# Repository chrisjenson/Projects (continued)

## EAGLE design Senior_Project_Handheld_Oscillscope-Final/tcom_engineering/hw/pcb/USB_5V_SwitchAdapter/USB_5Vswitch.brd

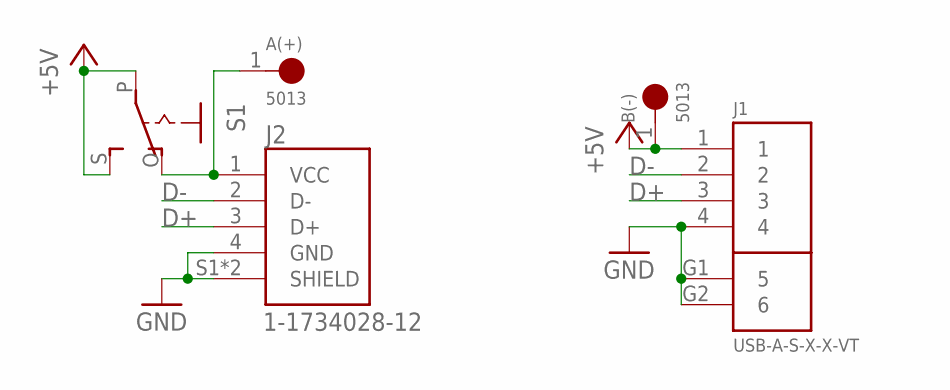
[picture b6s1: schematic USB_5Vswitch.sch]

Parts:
A(+): 5013; TESTPOINT_5013
B(-): 5013; TESTPOINT_5013
J1: USB-A-S-X-X-VT
J2: 1-1734028-12; TE_1-1734028-2
S1: EG1218S; EG1218

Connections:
+5V: B(-).1, J1.1, S1.P, S1.S
D+: J1.3, J2.3 (D+)
D-: J1.2, J2.2 (D-)
GND: J1.4, J1.G1 (5), J1.G2 (6), J2.4 (GND), J2.S1 (SHIELD), J2.S2 (SHIELD)
unnamed: A(+).1, J2.1 (VCC), S1.O

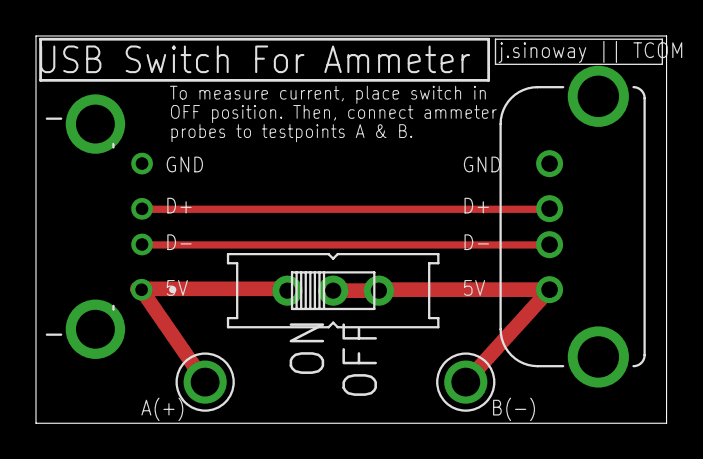
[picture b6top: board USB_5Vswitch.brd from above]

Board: 2 copper layers, 35.0 x 21.5 mm, 5 parts (0 on the bottom side), 5 nets.

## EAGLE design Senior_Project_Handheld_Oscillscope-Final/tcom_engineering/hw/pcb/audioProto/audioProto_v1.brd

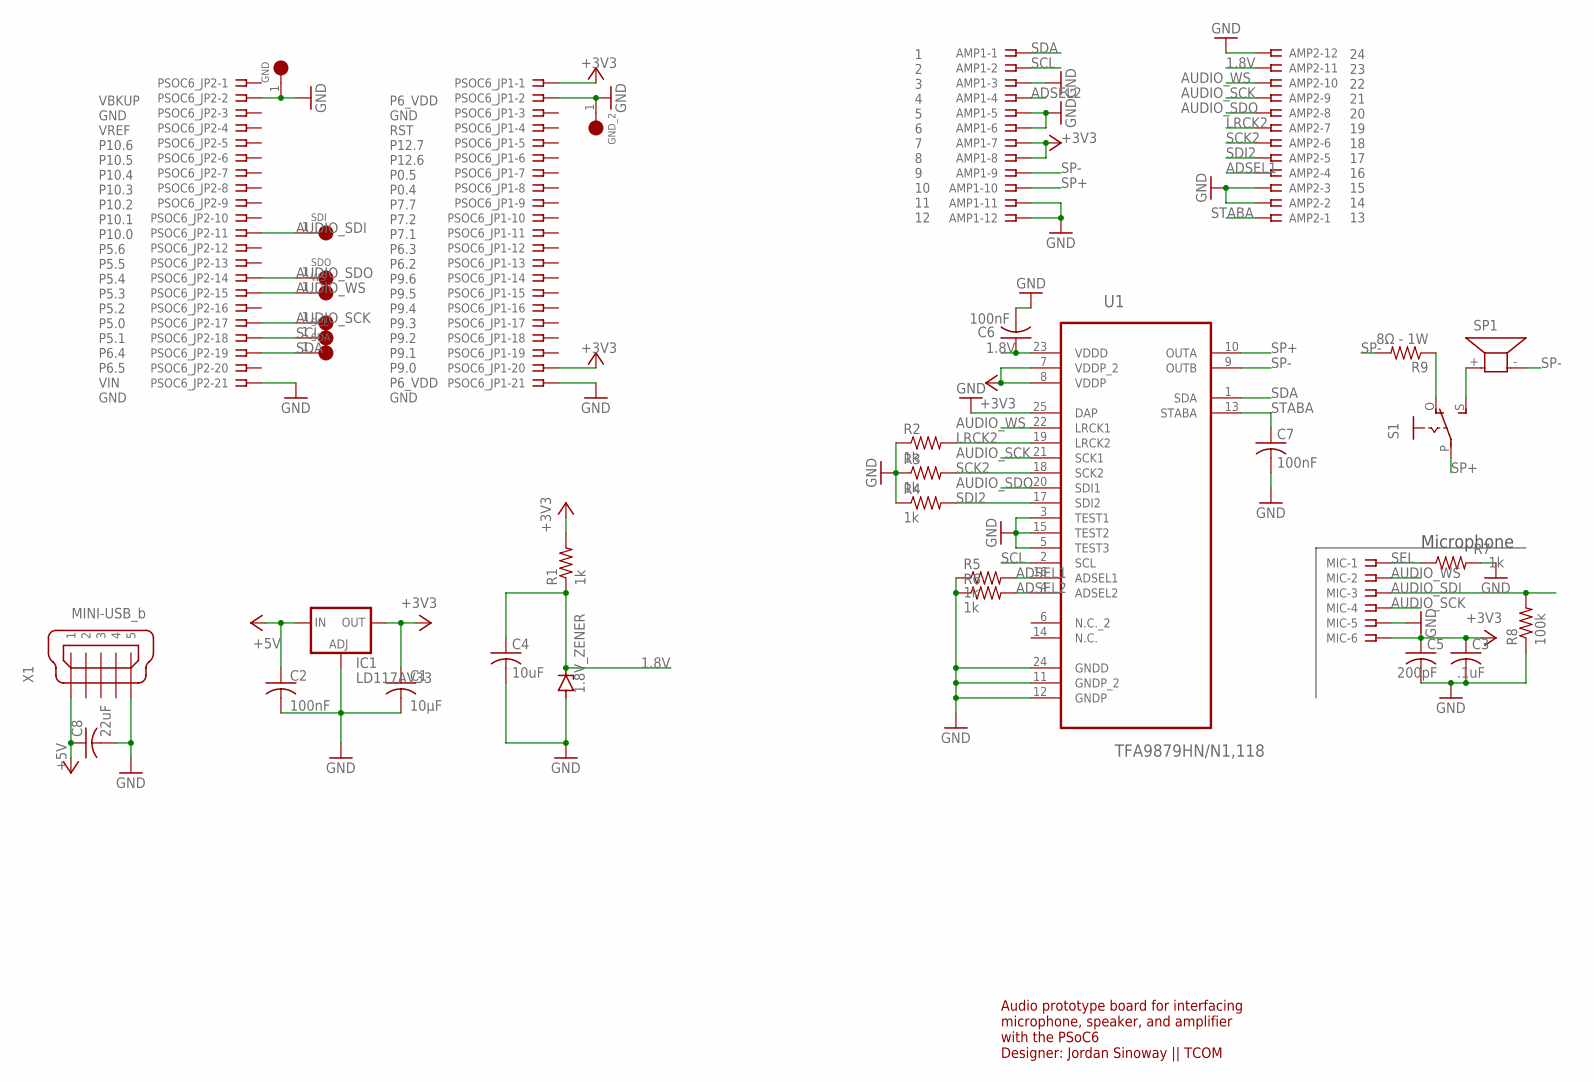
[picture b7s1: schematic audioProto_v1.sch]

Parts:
1.8V_ZENER: BZV10; DO34Z7
AMP1, AMP2: SSW-112-02-G-S
C1: 10μF; C050-024X044
C2, C6, C7: 100nF; C050-024X044
C3: .1uF; C050-024X044
C4: 10uF; C050-024X044
C5: 200pF; C050-024X044
C8: 22uF; C050-024X044
GND: 5013; TESTPOINT_5013
GND_2: 5013; TESTPOINT_5013
IC1: LD117AV33; TO220L1
MIC: SSW-106-02-G-S
PSOC6_JP1, PSOC6_JP2: SSW-121-02-G-S
R1, R2, R3, R4, R5, R6: 1k; 0204/7
R7: 1k; 0207/9
R8: 100k; 0207/9
R9: 8Ω - 1W; 0207/10
S1: EG1218S; EG1218
SCK: 5013; TESTPOINT_5013
SCL: 5013; TESTPOINT_5013
SDA: 5013; TESTPOINT_5013
SDI: 5013; TESTPOINT_5013
SDO: 5013; TESTPOINT_5013
SP1: KSS1201
U1: TFA9879HN/N1,118; QFN50P260X260X100-25N
WS: 5013; TESTPOINT_5013
X1: MINI-USB_b; 32005-601

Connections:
1.8V: 1.8V_ZENER.C, AMP2.11, C4.1, C6.1, R1.1, U1.23 (VDDD)
+3V3: AMP1.7, AMP1.8, C1.1, C3.1, C5.1, IC1.2 (OUT), MIC.6, PSOC6_JP1.1, PSOC6_JP1.20, R1.2, U1.7 (VDDP_2), U1.8 (VDDP)
+5V: C2.1, C8.1, IC1.3 (IN), X1.1
ADSEL1: AMP2.4, R5.2, U1.16 (ADSEL1)
ADSEL2: AMP1.4, R6.2, U1.4 (ADSEL2)
AUDIO_SCK: AMP2.9, MIC.4, PSOC6_JP2.17, SCK.1, U1.21 (SCK1)
AUDIO_SDI: MIC.3, PSOC6_JP2.11, R8.2, SDI.1
AUDIO_SDO: AMP2.8, PSOC6_JP2.14, SDO.1, U1.20 (SDI1)
AUDIO_WS: AMP2.10, MIC.2, PSOC6_JP2.15, U1.22 (LRCK1), WS.1
GND: 1.8V_ZENER.A, AMP1.3, AMP1.5, AMP1.6, AMP1.11, AMP1.12, AMP2.2, AMP2.3, AMP2.12, C1.2, C2.2, C3.2, C4.2, C5.2, C6.2, C7.2, C8.2, GND.1, GND_2.1, IC1.1 (ADJ), MIC.5, PSOC6_JP1.2, PSOC6_JP1.21, PSOC6_JP2.2, PSOC6_JP2.21, R2.1, R3.1, R4.1, R5.1, R6.1, R7.2, R8.1, U1.3 (TEST1), U1.5 (TEST3), U1.11 (GNDP_2), U1.12 (GNDP), U1.15 (TEST2), U1.24 (GNDD), U1.25 (DAP), X1.5
LRCK2: AMP2.7, R2.2, U1.19 (LRCK2)
unnamed: R9.1, S1.O
unnamed: S1.S, SP1.+ (1)
SCK2: AMP2.6, R3.2, U1.18 (SCK2)
SCL: AMP1.2, PSOC6_JP2.18, SCL.1, U1.2 (SCL)
SDA: AMP1.1, PSOC6_JP2.19, SDA.1, U1.1 (SDA)
SDI2: AMP2.5, R4.2, U1.17 (SDI2)
SEL: MIC.1, R7.1
SP+: AMP1.10, S1.P, U1.10 (OUTA)
SP-: AMP1.9, R9.2, SP1.- (2), U1.9 (OUTB)
STABA: AMP2.1, C7.1, U1.13 (STABA)

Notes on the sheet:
VBKUP GND VREF P10.6 P10.5 P10.4 P10.3 P10.2 P10.1 P10.0 P5.6 P5.5 P5.4 P5.3 P5.2 P5.0 P5.1 P6.4 P6.5 VIN GND
P6_VDD GND RST P12.7 P12.6 P0.5 P0.4 P7.7 P7.2 P7.1 P6.3 P6.2 P9.6 P9.5 P9.4 P9.3 P9.2 P9.1 P9.0 P6_VDD GND
Microphone
1 2 3 4 5 6 7 8 9 10 11 12
24 23 22 21 20 19 18 17 16 15 14 13
Audio prototype board for interfacing microphone, speaker, and amplifier with the PSoC6 Designer: Jordan Sinoway || TCOM

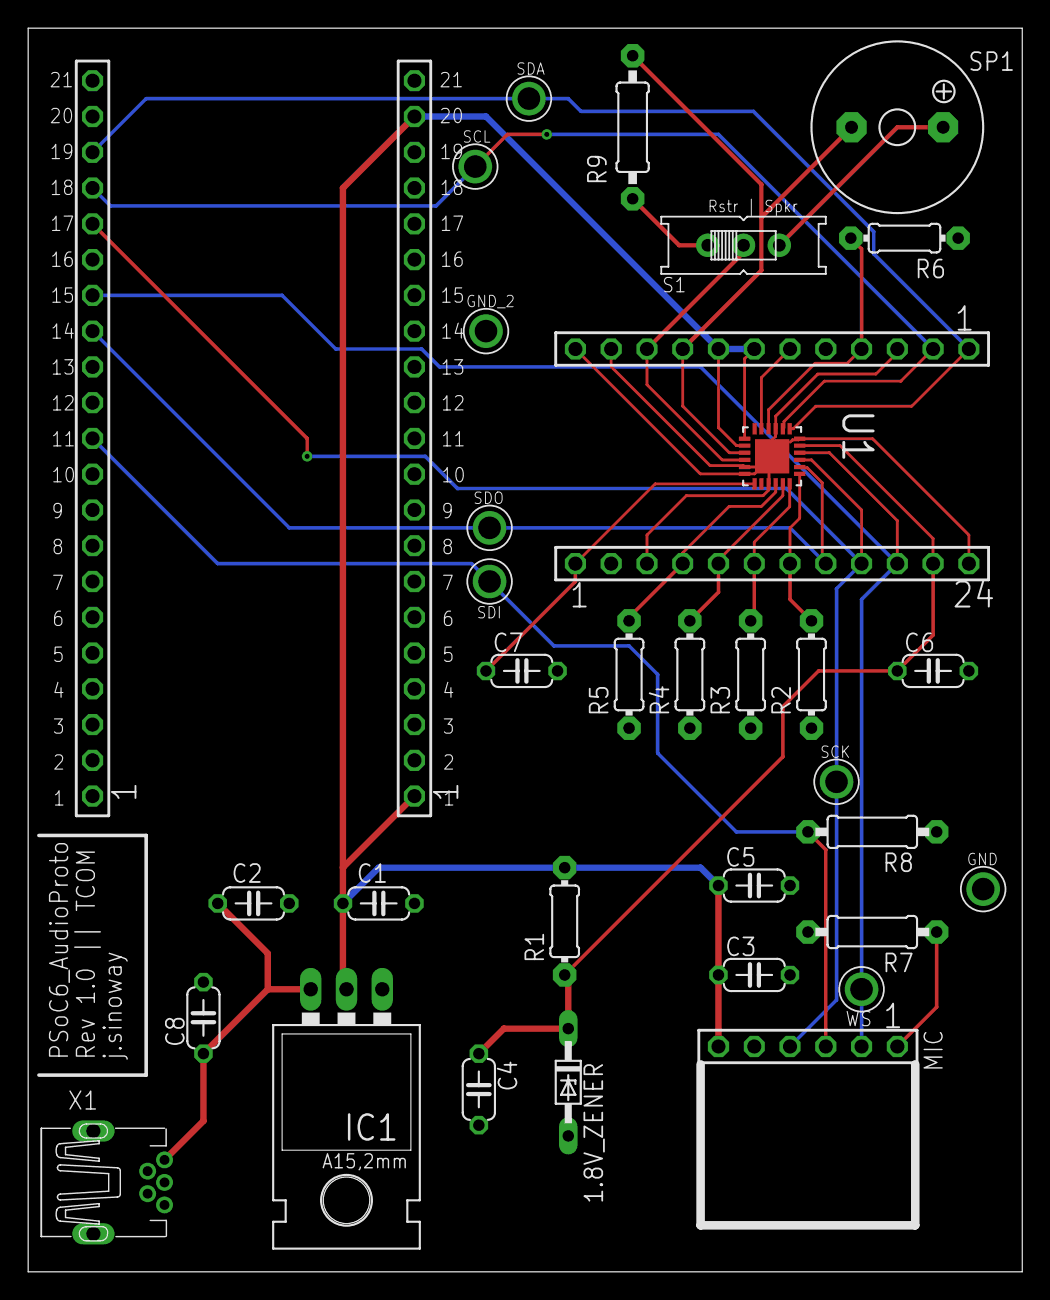
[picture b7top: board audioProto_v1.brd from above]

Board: 2 copper layers, 70.6 x 88.3 mm, 36 parts (0 on the bottom side), 21 nets.

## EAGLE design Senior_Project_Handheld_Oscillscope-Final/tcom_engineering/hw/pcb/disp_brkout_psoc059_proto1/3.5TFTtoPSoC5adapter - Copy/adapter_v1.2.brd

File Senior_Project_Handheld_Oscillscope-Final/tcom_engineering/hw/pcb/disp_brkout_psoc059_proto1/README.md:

# disp_brkout_psoc059_proto1
Eagle database for display breakout board to PSoC 5LP 059 board.

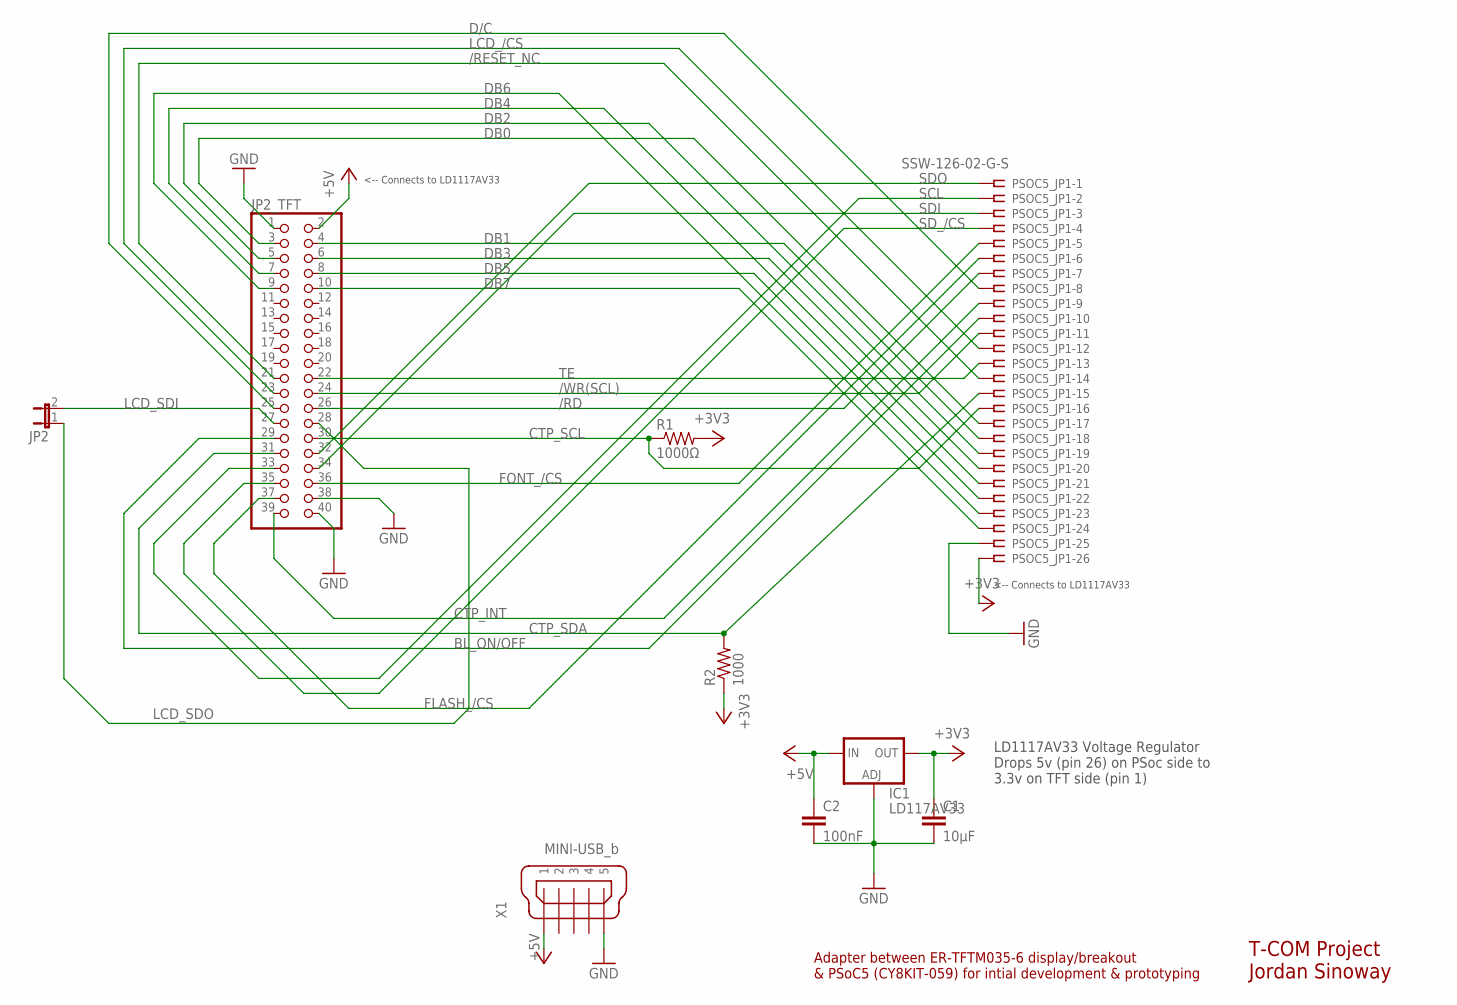
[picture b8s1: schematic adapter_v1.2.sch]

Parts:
C1: 10μF; C2.5-2
C2: 100nF; C2.5-2
IC1: LD117AV33; TO220L1
JP2: JP1E; JP1
JP2_TFT: PINHD-2X20; 2X20
PSOC5_JP1: SSW-126-02-G-S
R1: 1000Ω; 0204/7
R2: 1000; 0204/7
X1: MINI-USB_b; 32005-601

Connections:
+3V3: C1.1, IC1.2 (OUT), PSOC5_JP1.26, R1.2, R2.1
+5V: C2.1, IC1.3 (IN), JP2_TFT.2, X1.1
/RD: JP2_TFT.26, PSOC5_JP1.7
/RESET_NC: JP2_TFT.21, PSOC5_JP1.14
/WR(SCL): JP2_TFT.24, PSOC5_JP1.11
BL_ON/OFF: JP2_TFT.29, PSOC5_JP1.10
CTP_INT: JP2_TFT.39, PSOC5_JP1.9
CTP_SCL: JP2_TFT.30, PSOC5_JP1.16, R1.1
CTP_SDA: JP2_TFT.31, PSOC5_JP1.15, R2.2
D/C: JP2_TFT.25, PSOC5_JP1.8
DB0: JP2_TFT.3, PSOC5_JP1.17
DB1: JP2_TFT.4, PSOC5_JP1.18
DB2: JP2_TFT.5, PSOC5_JP1.19
DB3: JP2_TFT.6, PSOC5_JP1.20
DB4: JP2_TFT.7, PSOC5_JP1.21
DB5: JP2_TFT.8, PSOC5_JP1.22
DB6: JP2_TFT.9, PSOC5_JP1.23
DB7: JP2_TFT.10, PSOC5_JP1.24
FLASH_/CS: JP2_TFT.37, PSOC5_JP1.6
FONT_/CS: JP2_TFT.36, PSOC5_JP1.5
GND: C1.2, C2.2, IC1.1 (ADJ), JP2_TFT.1, JP2_TFT.38, JP2_TFT.40, PSOC5_JP1.25, X1.5
LCD_/CS: JP2_TFT.23, PSOC5_JP1.12
LCD_SDI: JP2.2, JP2_TFT.27
LCD_SDO: JP2.1, JP2_TFT.28
SCL: JP2_TFT.33, PSOC5_JP1.2
SDI: JP2_TFT.34, PSOC5_JP1.3
SDO: JP2_TFT.32, PSOC5_JP1.1
SD_/CS: JP2_TFT.35, PSOC5_JP1.4
TE: JP2_TFT.22, PSOC5_JP1.13

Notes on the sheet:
LD1117AV33 Voltage Regulator Drops 5v (pin 26) on PSoc side to 3.3v on TFT side (pin 1)
<-- Connects to LD1117AV33
T-COM Project Jordan Sinoway
Adapter between ER-TFTM035-6 display/breakout & PSoC5 (CY8KIT-059) for intial development & prototyping

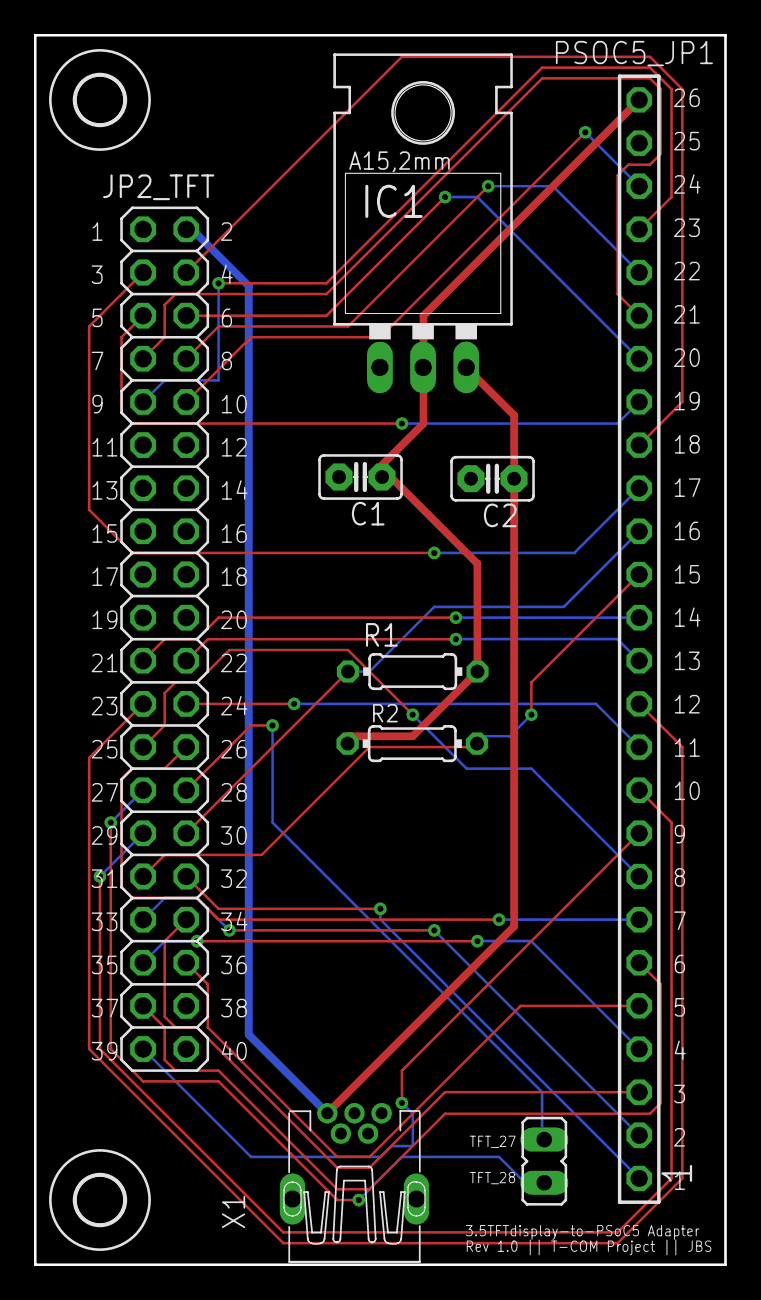
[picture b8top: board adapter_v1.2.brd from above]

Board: 2 copper layers, 40.6 x 72.4 mm, 11 parts (0 on the bottom side), 29 nets.

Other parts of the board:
U$1, U$2: 2,8

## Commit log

2019-12-20 uploading of the semesters noteworthy projects
2019-12-21 adding documentation
2019-12-21 format change
2019-12-21 added game development project
2019-12-21 addition of old coding assignments
2019-12-21 adding docs
2020-04-26 NLP projects added
2020-05-09 NLP project 4
2020-05-18 Addition of final NLP Project
2021-07-14 addition of senior year projects
2021-07-14 more projects
2021-07-14 OS proj 2 docs
2022-01-14 presentation with demo videos
